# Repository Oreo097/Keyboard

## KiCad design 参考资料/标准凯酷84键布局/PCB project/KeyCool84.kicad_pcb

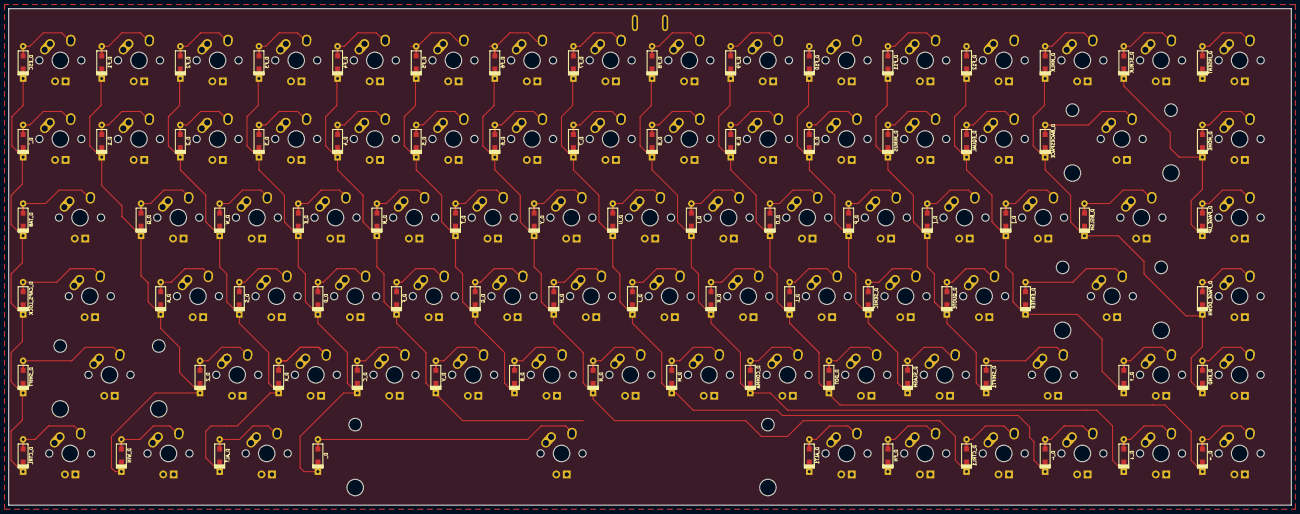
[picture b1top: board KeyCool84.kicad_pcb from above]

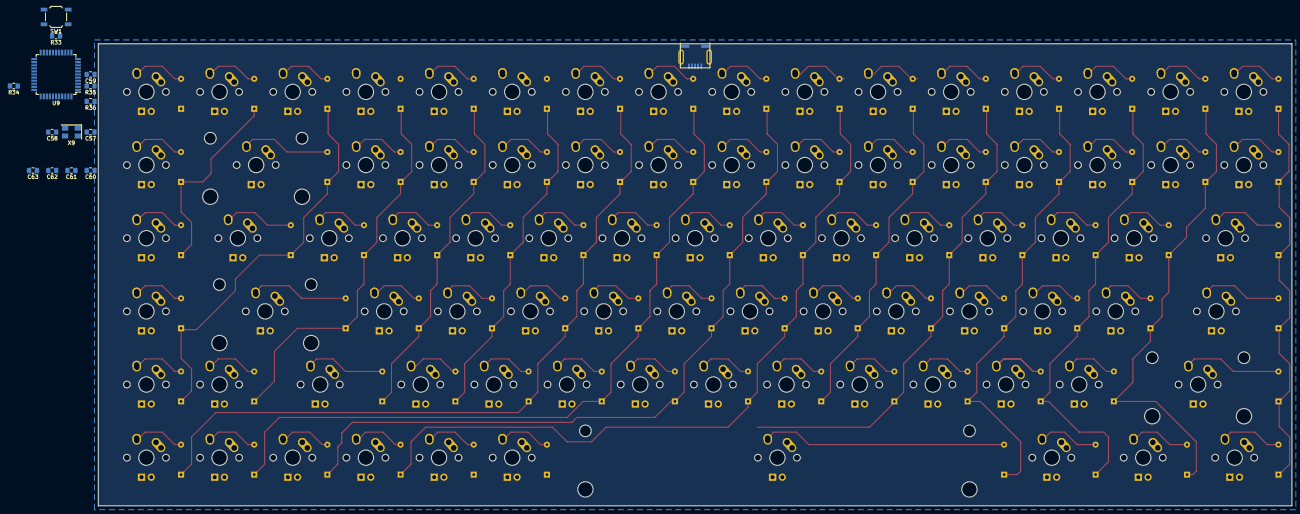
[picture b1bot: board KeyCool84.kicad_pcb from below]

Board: 2 copper layers, 310.8 x 120.3 mm, 183 parts (15 on the bottom side), 110 nets.

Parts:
C57, C58, C59, C60, C61, C62, C63: 22pF; C_0805_2012Metric_Pad1.15x1.40mm_HandSolder
D_, D_0, D_1, D_2, D_3, D_4, D_5, D_6, D_7, D_8, D_9: D; D_SOD123_axial
D_A: D; D_SOD123_axial
D_ALT, D_ALT1: D; D_SOD123_axial
D_B: D; D_SOD123_axial
D_BACKSPACE: D; D_SOD123_axial
D_BSLSH: D; D_SOD123_axial
D_C: D; D_SOD123_axial
D_CAPS_LOCK: D; D_SOD123_axial
D_COMMA: D; D_SOD123_axial
D_CTRL, D_CTRL1: D; D_SOD123_axial
D_D: D; D_SOD123_axial
D_DOT: D; D_SOD123_axial
D_E: D; D_SOD123_axial
D_END: D; D_SOD123_axial
D_ENTER: D; D_SOD123_axial
D_EQUAL: D; D_SOD123_axial
D_ESC: D; D_SOD123_axial
D_F, D_F1, D_F2, D_F3, D_F4, D_F5, D_F6, D_F7, D_F8, D_F9, D_F10, D_F11, D_F12: D; D_SOD123_axial
D_FN: D; D_SOD123_axial
D_G: D; D_SOD123_axial
D_H: D; D_SOD123_axial
D_HOME: D; D_SOD123_axial
D_I: D; D_SOD123_axial
D_INSERT: D; D_SOD123_axial
D_J: D; D_SOD123_axial
D_K: D; D_SOD123_axial
D_L: D; D_SOD123_axial
D_M: D; D_SOD123_axial
D_MINUS: D; D_SOD123_axial
D_N: D; D_SOD123_axial
D_NMLK: D; D_SOD123_axial
D_O: D; D_SOD123_axial
D_P: D; D_SOD123_axial
D_PAGE_DOWN: D; D_SOD123_axial
D_PAGE_UP: D; D_SOD123_axial
D_Q: D; D_SOD123_axial
D_QUOTE: D; D_SOD123_axial
D_R: D; D_SOD123_axial
D_S: D; D_SOD123_axial
D_SCRLK: D; D_SOD123_axial
D_SEMIC: D; D_SOD123_axial
D_SHIFT, D_SHIFT1: D; D_SOD123_axial
D_SLASH: D; D_SOD123_axial
D_T: D; D_SOD123_axial
D_TAB: D; D_SOD123_axial
D_U: D; D_SOD123_axial
D_V: D; D_SOD123_axial
D_W: D; D_SOD123_axial
D_WIN: D; D_SOD123_axial
D_X: D; D_SOD123_axial
D_Y: D; D_SOD123_axial
D_Z: D; D_SOD123_axial
D_[: D; D_SOD123_axial
D_]: D; D_SOD123_axial
D_`: D; D_SOD123_axial
D_←: D; D_SOD123_axial
D_↑: D; D_SOD123_axial
D_→: D; D_SOD123_axial
D_↓: D; D_SOD123_axial
K_: KEYSW; MX-6.25U-NoLED
K_0, K_1, K_2, K_3, K_4, K_5, K_6, K_7, K_8, K_9: KEYSW; MX-1U-NoLED
K_A: KEYSW; MX-1U-NoLED
K_ALT: KEYSW; MX-1.25U-NoLED
K_ALT1: KEYSW; MX-1U-NoLED
K_B: KEYSW; MX-1U-NoLED
K_BACKSPACE: KEYSW; MX-2U-NoLED
K_BSLSH: KEYSW; MX-1.5U-NoLED
K_C: KEYSW; MX-1U-NoLED
K_CAPS_LOCK: KEYSW; MX-1.75U-NoLED
K_COMMA: KEYSW; MX-1U-NoLED
K_CTRL: KEYSW; MX-1.25U-NoLED
K_CTRL1: KEYSW; MX-1U-NoLED
K_D: KEYSW; MX-1U-NoLED
K_DOT: KEYSW; MX-1U-NoLED
K_E: KEYSW; MX-1U-NoLED
K_END: KEYSW; MX-1U-NoLED
K_ENTER: KEYSW; MX-2.25U-NoLED
K_EQUAL: KEYSW; MX-1U-NoLED
K_ESC: KEYSW; MX-1U-NoLED
K_F, K_F1, K_F2, K_F3, K_F4, K_F5, K_F6, K_F7, K_F8, K_F9, K_F10, K_F11, K_F12: KEYSW; MX-1U-NoLED
K_FN: KEYSW; MX-1U-NoLED
K_G: KEYSW; MX-1U-NoLED
K_H: KEYSW; MX-1U-NoLED
K_HOME: KEYSW; MX-1U-NoLED
K_I: KEYSW; MX-1U-NoLED
K_INSERT: KEYSW; MX-1U-NoLED
K_J: KEYSW; MX-1U-NoLED
K_K: KEYSW; MX-1U-NoLED
K_L: KEYSW; MX-1U-NoLED
K_M: KEYSW; MX-1U-NoLED
K_MINUS: KEYSW; MX-1U-NoLED
K_N: KEYSW; MX-1U-NoLED
K_NMLK: KEYSW; MX-1U-NoLED
K_O: KEYSW; MX-1U-NoLED
K_P: KEYSW; MX-1U-NoLED
K_PAGE_DOWN: KEYSW; MX-1U-NoLED
K_PAGE_UP: KEYSW; MX-1U-NoLED
K_Q: KEYSW; MX-1U-NoLED
K_QUOTE: KEYSW; MX-1U-NoLED
K_R: KEYSW; MX-1U-NoLED
K_S: KEYSW; MX-1U-NoLED
K_SCRLK: KEYSW; MX-1U-NoLED
K_SEMIC: KEYSW; MX-1U-NoLED
K_SHIFT: KEYSW; MX-2.25U-NoLED
K_SHIFT1: KEYSW; MX-1.75U-NoLED
K_SLASH: KEYSW; MX-1U-NoLED
K_T: KEYSW; MX-1U-NoLED
K_TAB: KEYSW; MX-1.5U-NoLED
K_U: KEYSW; MX-1U-NoLED
K_V: KEYSW; MX-1U-NoLED
K_W: KEYSW; MX-1U-NoLED
K_WIN: KEYSW; MX-1.25U-NoLED
K_X: KEYSW; MX-1U-NoLED
K_Y: KEYSW; MX-1U-NoLED
K_Z: KEYSW; MX-1U-NoLED
K_[: KEYSW; MX-1U-NoLED
K_]: KEYSW; MX-1U-NoLED
K_`: KEYSW; MX-1U-NoLED
K_←: KEYSW; MX-1U-NoLED
K_↑: KEYSW; MX-1U-NoLED
K_→: KEYSW; MX-1U-NoLED
K_↓: KEYSW; MX-1U-NoLED
R33, R34: 10k; R_0805_2012Metric_Pad1.15x1.40mm_HandSolder
R35, R36: 22u; R_0805_2012Metric_Pad1.15x1.40mm_HandSolder
SW1: SW_PUSH; SW_SPST_TL3342
U9: ATMEGA32U4; TQFP-44_10x10mm_P0.8mm
USB9: USB_mini_micro_B; USB_miniB_hirose_5S8
X9: XTAL_GND; Crystal_SMD_5032-4Pin_5.0x3.2mm

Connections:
/col0: D_CAPS_LOCK.1, D_CTRL.1, D_ESC.1, D_SHIFT.1, D_TAB.1, D_`.1, U9.32
/col1: D_1.1, D_A.1, D_F1.1, D_Q.1, D_WIN.1, D_Z.1, U9.31
/col2: D_2.1, D_ALT.1, D_F2.1, D_S.1, D_W.1, D_X.1, U9.12
/col3: D_.1, D_3.1, D_C.1, D_D.1, D_E.1, D_F3.1, U9.30
/col4: D_4.1, D_ALT1.1, D_F.1, D_F4.1, D_R.1, D_V.1, U9.29
/col5: D_5.1, D_B.1, D_F5.1, D_FN.1, D_G.1, D_T.1, U9.28
/col6: D_6.1, D_CTRL1.1, D_F6.1, D_H.1, D_N.1, D_Y.1, U9.11
/col7: D_7.1, D_F7.1, D_J.1, D_M.1, D_U.1, D_←.1, U9.10
/col8: D_8.1, D_COMMA.1, D_F8.1, D_I.1, D_K.1, D_↓.1, U9.9
/col9: D_9.1, D_DOT.1, D_F9.1, D_L.1, D_O.1, D_→.1, U9.8
/col10: D_0.1, D_F10.1, D_P.1, D_SEMIC.1, D_SLASH.1, U9.37
/col11: D_F11.1, D_MINUS.1, D_QUOTE.1, D_SHIFT1.1, D_[.1, U9.38
/col12: D_ENTER.1, D_EQUAL.1, D_F12.1, D_].1, D_↑.1, U9.39
/col13: D_BACKSPACE.1, D_BSLSH.1, D_END.1, D_NMLK.1, D_PAGE_DOWN.1, U9.40
/col14: D_HOME.1, D_PAGE_UP.1, D_SCRLK.1, U9.41
GND: C57.2, C58.2, C59.2, C60.2, C61.2, C62.2, C63.2, R34.2, SW1.1, U9.5, U9.15, U9.23, USB9.5, USB9.6, X9.3
unnamed: C57.1, U9.16
unnamed: C58.1, U9.17
unnamed: C59.1, U9.6
unnamed: D_0.2, K_0.2
unnamed: D_1.2, K_1.2
unnamed: D_2.2, K_2.2
unnamed: D_3.2, K_3.2
unnamed: D_4.2, K_4.2
unnamed: D_5.2, K_5.2
unnamed: D_6.2, K_6.2
unnamed: D_7.2, K_7.2
unnamed: D_8.2, K_8.2
unnamed: D_9.2, K_9.2
unnamed: D_.2, K_.2
unnamed: D_A.2, K_A.2
unnamed: D_ALT1.2, K_ALT1.2
unnamed: D_ALT.2, K_ALT.2
unnamed: D_B.2, K_B.2
unnamed: D_BACKSPACE.2, K_BACKSPACE.2
unnamed: D_BSLSH.2, K_BSLSH.2
unnamed: D_C.2, K_C.2
unnamed: D_CAPS_LOCK.2, K_CAPS_LOCK.2
unnamed: D_COMMA.2, K_COMMA.2
unnamed: D_CTRL1.2, K_CTRL1.2
unnamed: D_CTRL.2, K_CTRL.2
unnamed: D_D.2, K_D.2
unnamed: D_DOT.2, K_DOT.2
unnamed: D_E.2, K_E.2
unnamed: D_END.2, K_END.2
unnamed: D_ENTER.2, K_ENTER.2
unnamed: D_EQUAL.2, K_EQUAL.2
unnamed: D_ESC.2, K_ESC.2
unnamed: D_F1.2, K_F1.2
unnamed: D_F2.2, K_F2.2
unnamed: D_F3.2, K_F3.2
unnamed: D_F4.2, K_F4.2
unnamed: D_F5.2, K_F5.2
unnamed: D_F6.2, K_F6.2
unnamed: D_F7.2, K_F7.2
unnamed: D_F8.2, K_F8.2
unnamed: D_F9.2, K_F9.2
unnamed: D_F10.2, K_F10.2
unnamed: D_F11.2, K_F11.2
unnamed: D_F12.2, K_F12.2
unnamed: D_F.2, K_F.2
unnamed: D_FN.2, K_FN.2
unnamed: D_G.2, K_G.2
unnamed: D_H.2, K_H.2
unnamed: D_HOME.2, K_HOME.2
unnamed: D_I.2, K_I.2
unnamed: D_INSERT.2, K_INSERT.2
unnamed: D_J.2, K_J.2
unnamed: D_K.2, K_K.2
unnamed: D_L.2, K_L.2
unnamed: D_M.2, K_M.2
unnamed: D_MINUS.2, K_MINUS.2
unnamed: D_N.2, K_N.2
unnamed: D_NMLK.2, K_NMLK.2
unnamed: D_O.2, K_O.2
unnamed: D_P.2, K_P.2
unnamed: D_PAGE_DOWN.2, K_PAGE_DOWN.2
unnamed: D_PAGE_UP.2, K_PAGE_UP.2
unnamed: D_Q.2, K_Q.2
unnamed: D_QUOTE.2, K_QUOTE.2
unnamed: D_R.2, K_R.2
unnamed: D_S.2, K_S.2
unnamed: D_SCRLK.2, K_SCRLK.2
unnamed: D_SEMIC.2, K_SEMIC.2
unnamed: D_SHIFT1.2, K_SHIFT1.2
unnamed: D_SHIFT.2, K_SHIFT.2
unnamed: D_SLASH.2, K_SLASH.2
unnamed: D_T.2, K_T.2
unnamed: D_TAB.2, K_TAB.2
unnamed: D_U.2, K_U.2
unnamed: D_V.2, K_V.2
unnamed: D_W.2, K_W.2
unnamed: D_WIN.2, K_WIN.2
unnamed: D_X.2, K_X.2
unnamed: D_Y.2, K_Y.2
unnamed: D_Z.2, K_Z.2
unnamed: D_[.2, K_[.2
unnamed: D_].2, K_].2
unnamed: D_`.2, K_`.2
unnamed: D_←.2, K_←.2
unnamed: D_↑.2, K_↑.2
unnamed: D_→.2, K_→.2
unnamed: D_↓.2, K_↓.2
unnamed: R33.1, SW1.2, U9.13
unnamed: R34.1, U9.33
unnamed: R35.1, U9.3
unnamed: R36.1, U9.4
unnamed: R35.2, USB9.2
unnamed: R36.2, USB9.3
VCC: C60.1, C61.1, C62.1, C63.1, R33.2, U9.2, U9.14, U9.24, USB9.1

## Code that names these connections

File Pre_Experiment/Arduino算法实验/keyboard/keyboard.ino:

/*这是前期实验Arduino算法，主要用于扫描算法的检查*/

#define LED 2

#define Row1 3
#define Row2 4

#define Col1 5
#define Col2 6
#define Col3 7
#define Col4 8
#define Col5 9
#define Col6 10

void setup()
{
  // put your setup code here, to run once:
  pinMode(LED, OUTPUT);
  digitalWrite(LED, HIGH);
  pinMode(Row1, INPUT);
  pinMode(Row2, INPUT);

  pinMode(Col1, OUTPUT);
  pinMode(Col2, OUTPUT);
  pinMode(Col3, OUTPUT);
  pinMode(Col4, OUTPUT);
  pinMode(Col5, OUTPUT);
  delay(500);
  digitalWrite(LED, LOW);
  Serial.begin(9600);
  delay(500);
}

void loop()
{
  struct matrix
  {
    int key[12] = {0};
    int *inter = key;
  } matrix;
  digitalWrite(LED, HIGH);
  digitalWrite(Col1, HIGH);
  digitalWrite(Col2, LOW);
  digitalWrite(Col3, LOW);
  digitalWrite(Col4, LOW);
  digitalWrite(Col5, LOW);
  digitalWrite(Col6, LOW);
  delay(1); //延迟1ms使电平平稳
  if (digitalRead(Row1) == HIGH)
  {
    *matrix.inter = 1;
    matrix.inter++;
  }
  if (digitalRead(Row2) == HIGH)
  {
    *matrix.inter = 1;
    matrix.inter++;
  }

  digitalWrite(Col1, LOW);
  digitalWrite(Col2, HIGH);
  digitalWrite(Col3, LOW);
  digitalWrite(Col4, LOW);
  digitalWrite(Col5, LOW);
  digitalWrite(Col6, LOW);
  delay(1); //延迟1ms使电平平稳
  if (digitalRead(Row1) == HIGH)
  {
    *matrix.inter = 1;
    matrix.inter++;
  }
  if (digitalRead(Row2) == HIGH)
  {
    *matrix.inter = 1;
    matrix.inter++;
  }
  digitalWrite(Col1, LOW);
  digitalWrite(Col2, LOW);
  digitalWrite(Col3, HIGH);
  digitalWrite(Col4, LOW);
  digitalWrite(Col5, LOW);
  digitalWrite(Col6, LOW);
  delay(1); //延迟1ms使电平平稳
  if (digitalRead(Row1) == HIGH)
  {
    *matrix.inter = 1;
    matrix.inter++;
  }
  if (digitalRead(Row2) == HIGH)
  {
    *matrix.inter = 1;
    matrix.inter++;
  }
  digitalWrite(Col1, LOW);
  digitalWrite(Col2, LOW);
  digitalWrite(Col3, LOW);
  digitalWrite(Col4, HIGH);
  digitalWrite(Col5, LOW);
  digitalWrite(Col6, LOW);
  delay(1); //延迟1ms使电平平稳
  if (digitalRead(Row1) == HIGH)
  {
    *matrix.inter = 1;
    matrix.inter++;
  }
  if (digitalRead(Row2) == HIGH)
  {
    *matrix.inter = 1;
    matrix.inter++;
  }
  digitalWrite(Col1, LOW);
  digitalWrite(Col2, LOW);
  digitalWrite(Col3, LOW);
  digitalWrite(Col4, LOW);
  digitalWrite(Col5, HIGH);
  digitalWrite(Col6, LOW);
  delay(1); //延迟1ms使电平平稳
  if (digitalRead(Row1) == HIGH)
  {
    *matrix.inter = 1;
    matrix.inter++;
  }
  if (digitalRead(Row2) == HIGH)
  {
    *matrix.inter = 1;
    matrix.inter++;
  }
  digitalWrite(Col1, LOW);
  digitalWrite(Col2, LOW);
  digitalWrite(Col3, LOW);
  digitalWrite(Col4, LOW);
  digitalWrite(Col5, LOW);
  digitalWrite(Col6, HIGH);
  delay(1); //延迟1ms使电平平稳
  if (digitalRead(Row1) == HIGH)
  {
    *matrix.inter = 1;
    matrix.inter++;
  }
  if (digitalRead(Row2) == HIGH)
  {
    *matrix.inter = 1;
    matrix.inter++;
  }
  for (int i = 0; i < 12; i++)
  {
    Serial.println(matrix.key[i]);
    delay(2);
  }
  delay(500);
}

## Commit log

2020-03-27 new file: DIY_Project/Four Keys Keyboard/Firmware/Firmware_V1.hex new file: "DIY_Project/Four Keys Keyboard/\345\216\237\347\220\206\345\233\276\343\200\201PCB/FourKeysKeyboard.PcbDoc" new file: "DIY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
2020-03-30 new file: "\345\217\202\350\200\203\350\265\204\346\226\231/USB_HID\345\215\217\350\256\256/hid1_11.pdf" new file: "\345\217\202\350\200\203\350\265\204\346\226\231/qmk\351\224\256\347\233\230\345\23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
2020-03-31 new file: Screenshot_2020-03-28-22-34-05-187_com.taobao.idl.jpg new file: "\345\211\215\346\234\237\345\256\236\351\252\214/\346\225\260\345\255\227\351\224\256\347\233\230\345\256\232\344\275\215\34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
2020-04-02 添加了设设计原则，项目正式上马
2020-04-02 add some refence
2020-04-02 renamed: "\345\211\215\346\234\237\345\256\236\351\252\214/\346\225\260\345\255\227\351\224\256\347\233\230\345\256\232\344\275\215\346\235\277.dxf" -> "\345\211\215\346\234\237\345\256\236\351\252\2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
2020-04-02 renamed: "\345\211\215\346\234\237\345\256\236\351\252\214/\345\233\276\347\272\270/\345\256\232\344\275\215\346\235\277/\346\225\260\345\255\227\351\224\256\347\233\230\345\256\232\344\275\215\346\2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
2020-04-02 new file: "\345\211\215\346\234\237\345\256\236\351\252\214/\345\233\276\347\272\270/\345\244\226\345\243\263/~$\345\210\235\347\272\247\347\273\204\350\243\205.SLDASM" new file: "\345\211\215\346\23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
2020-04-03 new file: "\345\217\202\350\200\203\350\265\204\346\226\231/\345\233\275\345\244\226\345\205\250\351\200\217\346\230\216\351\224\256\347\233\230.jpg"
2020-04-03 deleted: "\350\256\276\350\256\241\345\216\237\345\210\231/AD\350\256\276\350\256\241\345\216\237\345\210\231.code" deleted: "\350\256\276\350\256\241\345\216\237\345\210\231/\344\270\273\346\216\247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
2020-04-03 deleted: "\345\211\215\346\234\237\345\256\236\351\252\214/\345\233\276\347\272\270/\345\244\226\345\243\263/~$\345\210\235\347\272\247\347\273\204\350\243\205.SLDASM" deleted: "\345\211\215\346\234\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
2020-04-03 modified: "\345\207\257\351\205\26784\351\224\256\347\233\230\345\217\202\346\225\260/\351\224\256\347\233\230\345\217\202\346\225\260.code"
2020-04-03 renamed: "\347\275\227\346\212\200K230\347\237\251\351\230\265.jpg" -> "\344\270\273\346\216\247\347\237\251\351\230\265\350\265\204\346\226\231/\347\275\227\346\212\200K230\347\237\251\351\230\265.j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
2020-04-03 new file: "\345\205\266\351\224\256\347\233\230\350\265\204\346\226\231/DIY_Project/Four Keys Keyboard/Firmware/Firmware_V1.hex" new file: "\345\205\266\351\224\256\347\233\230\350\265\204\346\226\23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
2020-04-04 renamed: "DIY_Project/Four Keys Keyboard/\345\216\237\347\220\206\345\233\276\343\200\201PCB/FourKeysKeyboard.PcbLib" -> "AD\345\272\223/FourKeysKeyboard.PcbLib" renamed: FourKeysKeyboard.SCHLIB -> "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
2020-04-05 modified: "\345\211\215\346\234\237\345\256\236\351\252\214/\345\233\276\347\272\270/\345\244\226\345\243\263/\345\260\217\351\224\256\347\233\230\347\273\204\350\243\205.SLDASM" new file: "\345\211\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
2020-04-08 new file: "\345\211\215\346\234\237\345\256\236\351\252\214/Arduino\347\256\227\346\263\225\345\256\236\351\252\214/keyboard/keyboard.ino"
2020-05-01 new file: "AD\345\272\223/History/KeyBoard.~(1).PcbLib.Zip" new file: "AD\345\272\223/History/KeyBoard.~(1).SchLib.Zip" new file: "AD\345\272\223/History/KeyBoard.~(10).PcbLib.Zip" new file: "AD\345\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
2020-05-01 new file: "AD\345\272\223/History/KeyBoard.~(13).PcbLib.Zip" new file: "AD\345\272\223/History/KeyBoard.~(14).PcbLib.Zip" modified: "AD\345\272\223/KeyBoard.PcbLib" new file: "\345\211\215\346\234\23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
2020-05-31 修改文件夹名称
2020-06-02 添加了新的资料“
2020-06-06 add stm32 kbd scan code
2020-06-07 modified: Inc/Serial_Log.h new file: Inc/debug.log modified: Inc/kbd_info.h modified: Inc/kbd_scan.h modified: MDK-ARM/kbd_scan.uvguix.ztdey modified: MDK-ARM/kbd_scan.uvprojx modified: Src/Serial_Lo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
2020-06-20 add the STM32 program with Number Pad
2020-06-20 prepare to use timer to start scan and rmjit
2020-06-21 add some usb hid file
2020-06-21 modified: Ghost_stm32_v0.1/Ghost_stm32_v0.1/Src/kbd_tim.c new file: Pre_Experiment/STM32/USBHID/.mxproject new file: Pre_Experiment/STM32/USBHID/Drivers/CMSIS/Core/Include/cmsis_armcc.h new file: Pre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
2020-06-22 modified: Inc/kbd_info.h new file: Inc/kbd_report.h modified: Inc/kbd_tim.h new file: Src/kbd_report.c modified: Src/kbd_tim.c modified: Src/tim.c
2020-06-22 modified: Ghost_stm32_v0.1/Ghost_stm32_v0.1/Src/kbd_report.c renamed: KBD_SCAN/kbd_scan/.mxproject -> Pre_Experiment/STM32/KBD_SCAN/kbd_scan/.mxproject renamed: KBD_SCAN/kbd_scan/.vs/ProjectSettings.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
2020-06-24 complete report making functions
2020-06-24 renamed: Ghost_stm32_v0.1/Ghost_stm32_v0.1/.mxproject -> Code/Ghost_stm32_v0.1/Ghost_stm32_v0.1/.mxproject renamed: Ghost_stm32_v0.1/Ghost_stm32_v0.1/Drivers/CMSIS/Core/Include/cmsis_armcc.h -> Code/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
2020-06-25 pre-ex add a hid experiment and reference add smoe doc
2020-06-26 modified: Code/Ghost_stm32_v0.1/Ghost_stm32_v0.1/Inc/kbd_func.h modified: Code/Ghost_stm32_v0.1/Ghost_stm32_v0.1/Inc/kbd_info.h modified: Code/Ghost_stm32_v0.1/Ghost_stm32_v0.1/Inc/kbd_report.h new f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
2020-06-26 modified: Code/Ghost_stm32_v0.1/Ghost_stm32_v0.1/Inc/kbd_func.h modified: Code/Ghost_stm32_v0.1/Ghost_stm32_v0.1/Inc/kbd_info.h modified: Code/Ghost_stm32_v0.1/Ghost_stm32_v0.1/Inc/kbd_report.h modif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
2020-06-28 modified: Code/Ghost_stm32_v0.1/Ghost_stm32_v0.1/Inc/kbd_scan.h modified: Code/Ghost_stm32_v0.1/Ghost_stm32_v0.1/Inc/kbd_serial.h modified: Code/Ghost_stm32_v0.1/Ghost_stm32_v0.1/MDK-ARM/Ghost_stm32_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
2020-06-29 modified: Code/Ghost_stm32_v0.1/Ghost_stm32_v0.1/Inc/kbd_info.h modified: Code/Ghost_stm32_v0.1/Ghost_stm32_v0.1/Inc/kbd_report.h modified: Code/Ghost_stm32_v0.1/Ghost_stm32_v0.1/Inc/kbd_scan.h modif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
2020-06-30 arrange some code
2020-06-30 add a new dexf of NUMPAD_BETA
2020-07-03 更新V0.5版本的软件
2020-07-04 添加了新的扫描函数
2020-07-05 修改了扫描函数的一些bug
2020-07-06 debug
2020-07-07 添加了一些注释
2020-07-07 添加了dbgmode选项
2020-07-07 添加头部注释
2020-07-07 修正注释内容
2020-07-07 modified: Code/Ghost_stm32_V0.5/Ghost_stm32_V0.5/Src/kbd_report.c
2020-07-07 modified: Code/Ghost_stm32_V0.5/Ghost_stm32_V0.5/Inc/kbd_func.h modified: Code/Ghost_stm32_V0.5/Ghost_stm32_V0.5/Inc/kbd_info.h modified: Code/Ghost_stm32_V0.5/Ghost_stm32_V0.5/Inc/kbd_report.h modif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
2020-07-08 modified: Code/Ghost_stm32_V0.5/Ghost_stm32_V0.5/Inc/kbd_info.h modified: Code/Ghost_stm32_V0.5/Ghost_stm32_V0.5/Inc/kbd_scan.h modified: Code/Ghost_stm32_V0.5/Ghost_stm32_V0.5/Src/kbd_func.c modifie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
2020-07-08 修改了6键冲突程序
2020-07-08 修改了逻辑结构，准备明天重写
2020-07-09 新建了v0.7版本的程序
2020-07-09 新建函数库
2020-07-09 重写了一部分函数
2020-07-10 完成了各子项扫描的函数，并写了一部分主扫描逻辑
2020-07-10 添加了debug框架文件，增加主逻辑结构，并在ans中添加了occupied
2020-07-10 试着编译了下，修改了些错误，但是并没有改变逻辑
2020-07-11 写了一部分dbg函数，和防抖函数
2020-07-11 modified: Code/Ghost_stm32_v0.7/Ghost_stm32_v0.7/Inc/kbd_param.h new file: Code/Ghost_stm32_v0.7/Ghost_stm32_v0.7/Inc/kbd_report.h modified: Code/Ghost_stm32_v0.7/Ghost_stm32_v0.7/Src/kbd_param.c new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
2020-07-12 modified: Code/Ghost_stm32_v0.7/Ghost_stm32_v0.7/Src/kbd_debug.c
2020-07-15 modified: Code/Ghost_stm32_v0.7/Ghost_stm32_v0.7/Src/kbd_param.c modified: Code/Ghost_stm32_v0.7/Ghost_stm32_v0.7/Src/kbd_report.c
2020-07-17 modified: Code/Ghost_stm32_v0.7/Ghost_stm32_v0.7/Src/kbd_scan.c
2020-07-19 modified: Code/Ghost_stm32_v0.7/Ghost_stm32_v0.7/Inc/kbd_debug.h modified: Code/Ghost_stm32_v0.7/Ghost_stm32_v0.7/Inc/kbd_func.h modified: Code/Ghost_stm32_v0.7/Ghost_stm32_v0.7/Inc/kbd_keyword.h mod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
2020-07-20 modified: "Pre_Experiment/\345\245\227\344\273\266\345\273\272\346\250\241\346\250\241\346\213\237/\345\256\232\344\275\215\346\235\277.SLDPRT"
2020-07-28 modified: Code/Ghost_stm32_v0.7/Ghost_stm32_v0.7/Inc/kbd_config.h modified: Code/Ghost_stm32_v0.7/Ghost_stm32_v0.7/Inc/kbd_debug.h modified: Code/Ghost_stm32_v0.7/Ghost_stm32_v0.7/Inc/kbd_report.h mo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
2020-07-30 new file: AD_Library/52832/EBYTE.PcbLib new file: AD_Library/52832/EBYTE.SchLib new file: AD_Library/52832/EBYTE52832.PrjPCB new file: AD_Library/52832/History/EBYTE.~(1).PcbLib.Zip new file: AD_Libr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
2020-08-01 modified: Code/Ghost_stm32_v0.7/Ghost_stm32_v0.7/Inc/kbd_config.h modified: Code/Ghost_stm32_v0.7/Ghost_stm32_v0.7/Inc/kbd_param.h modified: Code/Ghost_stm32_v0.7/Ghost_stm32_v0.7/Src/kbd_param.c mod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
2020-08-03 modified: Code/Ghost_stm32_v0.7/Ghost_stm32_v0.7/Inc/kbd_debug.h new file: Code/Ghost_stm32_v0.7/Ghost_stm32_v0.7/Inc/kbd_fkey.h new file: Code/Ghost_stm32_v0.7/Ghost_stm32_v0.7/Inc/kbd_main.h modifi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
2020-08-04 new file: .vs/Keyboard/v16/.suo new file: .vs/VSWorkspaceState.json new file: .vs/slnx.sqlite new file: Code/Ghost_stm32_v1.1/Ghost_stm32_v1.1/Inc/kbd_dbg.h new file: Code/Ghost_stm32_v1.1/Ghost_stm3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
2020-08-10 modified: Code/Ghost_stm32_v1.1/Ghost_stm32_v1.1/Inc/kbd_dbg.h modified: Code/Ghost_stm32_v1.1/Ghost_stm32_v1.1/Inc/kbd_scan.h modified: Code/Ghost_stm32_v1.1/Ghost_stm32_v1.1/Src/kbd_scan.c
2020-08-12 modified: Code/Ghost_stm32_v1.1/Ghost_stm32_v1.1/Inc/kbd_scan.h modified: Code/Ghost_stm32_v1.1/Ghost_stm32_v1.1/Src/kbd_scan.c
2020-08-16 modified: .vs/slnx.sqlite modified: Code/Ghost_stm32_v1.1/Ghost_stm32_v1.1/Inc/kbd_layer.h modified: Code/Ghost_stm32_v1.1/Ghost_stm32_v1.1/Inc/kbd_scan.h modified: Code/Ghost_stm32_v1.1/Ghost_stm32_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
2020-08-17 modified: Code/Ghost_stm32_v1.1/Ghost_stm32_v1.1/Inc/kbd_layer.h modified: Code/Ghost_stm32_v1.1/Ghost_stm32_v1.1/Inc/kbd_scan.h modified: Code/Ghost_stm32_v1.1/Ghost_stm32_v1.1/Src/kbd_scan.c
2020-09-22 new file: MyDesign/plate20200921.dxf new file: QMK/test.hex new file: QMK/test.json
2020-09-28 deleted: AD_Library/History/KeyBoard.~(10).PcbLib.Zip new file: AD_Library/History/KeyBoard.~(10).SchLib.Zip deleted: AD_Library/History/KeyBoard.~(11).PcbLib.Zip new file: AD_Library/History/KeyBoar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
2020-09-29 modified: Core/Core.PrjPCB new file: Core/Core.PrjPCBStructure modified: Core/Core_1.SchDoc new file: Core/History/Core.~(2).PrjPCB.Zip new file: Core/History/Core_1.~(10).SchDoc.Zip new file: Core/H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
2020-09-30 modified: Core/Core.PrjPCB modified: Core/Core_1.SchDoc new file: Core/History/Core.~(3).PrjPCB.Zip new file: Core/History/Core.~(4).PrjPCB.Zip new file: Core/History/Core_1.~(13).SchDoc.Zip new file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
2020-09-30 modified: Core/Core.PrjPCB modified: Core/Core_1.SchDoc new file: Core/History/Core.~(5).PrjPCB.Zip new file: Core/History/Core_1.~(70).SchDoc.Zip new file: Core/History/Core_1.~(71).SchDoc.Zip new f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
2020-10-02 new file: Core/CoreV0.2/CoreV0.2.PrjPCB new file: Core/CoreV0.2/History/PCB1.~(1).PcbDoc.Zip new file: Core/CoreV0.2/History/PCB1.~(10).PcbDoc.Zip new file: Core/CoreV0.2/History/PCB1.~(11).PcbDoc.Zi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
2020-10-08 modified: Core/CoreV0.2/CoreV0.2.PrjPCB new file: Core/CoreV0.2/CoreV0.2.PrjPCBStructure new file: Core/CoreV0.2/History/CoreV0.2.~(1).PrjPCB.Zip new file: Core/CoreV0.2/History/CoreV0.2.~(2).PrjPCB.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
2020-10-09 deleted: AD_Library/52832/EBYTE.PcbLib deleted: AD_Library/52832/EBYTE.SchLib deleted: AD_Library/52832/EBYTE52832.PrjPCB deleted: AD_Library/52832/History/EBYTE.~(1).PcbLib.Zip deleted: AD_Library/5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
2020-10-10 modified: Core/__Previews/Core_1.SchDocPreview new file: "\346\225\260\345\255\227\345\260\217\351\224\256\347\233\230/CAD/PAD.bak" new file: "\346\225\260\345\255\227\345\260\217\351\224\256\347\233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
2020-10-11 modified: Code/Ghost_stm32_v0.7/Ghost_stm32_v0.7/MDK-ARM/Ghost_stm32_v0.7.uvguix.ztdey modified: Code/Ghost_stm32_v0.8/Ghost_stm32_v0.8/MDK-ARM/Ghost_stm32_v1.1.uvguix.ztdey modified: Code/Ghost_stm3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
2020-10-11 new file: printf/dbg.c new file: printf/dbg.h
2021-03-05 new file: Code/Ghost_stm32_v1.2/.mxproject new file: Code/Ghost_stm32_v1.2/Core/Inc/gpio.h new file: Code/Ghost_stm32_v1.2/Core/Inc/kbd_debug.h new file: Code/Ghost_stm32_v1.2/Core/Inc/kbd_functions.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
